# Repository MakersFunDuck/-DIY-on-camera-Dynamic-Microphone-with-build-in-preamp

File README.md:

# DIY on-camera Dynamic micrcophone with build-in preamp

This project is a dynamic microphone utilizing a cloned SM57 capsule. The circuit incorporates a THAT 1510 preamp and is powered by phantom power from the XLR input. It is also compatible with dynamic microphones that require phantom power. If you wish to use it this way, simply cut the solder bridges and connect the appropriate ones. Additionally, I’ve left two pins available in case you prefer to power the circuit externally (e.g., with a battery). You can adjust the gain using the onboard knob.

Capsule which I used :
https://s.click.aliexpress.com/e/_omLsn6Z

Microphone Foam
https://s.click.aliexpress.com/e/_oEmwhu5

## License

 See the [LICENSE](LICENSE) file for details.

inspired from : https://github.com/ojg/thatmicpre

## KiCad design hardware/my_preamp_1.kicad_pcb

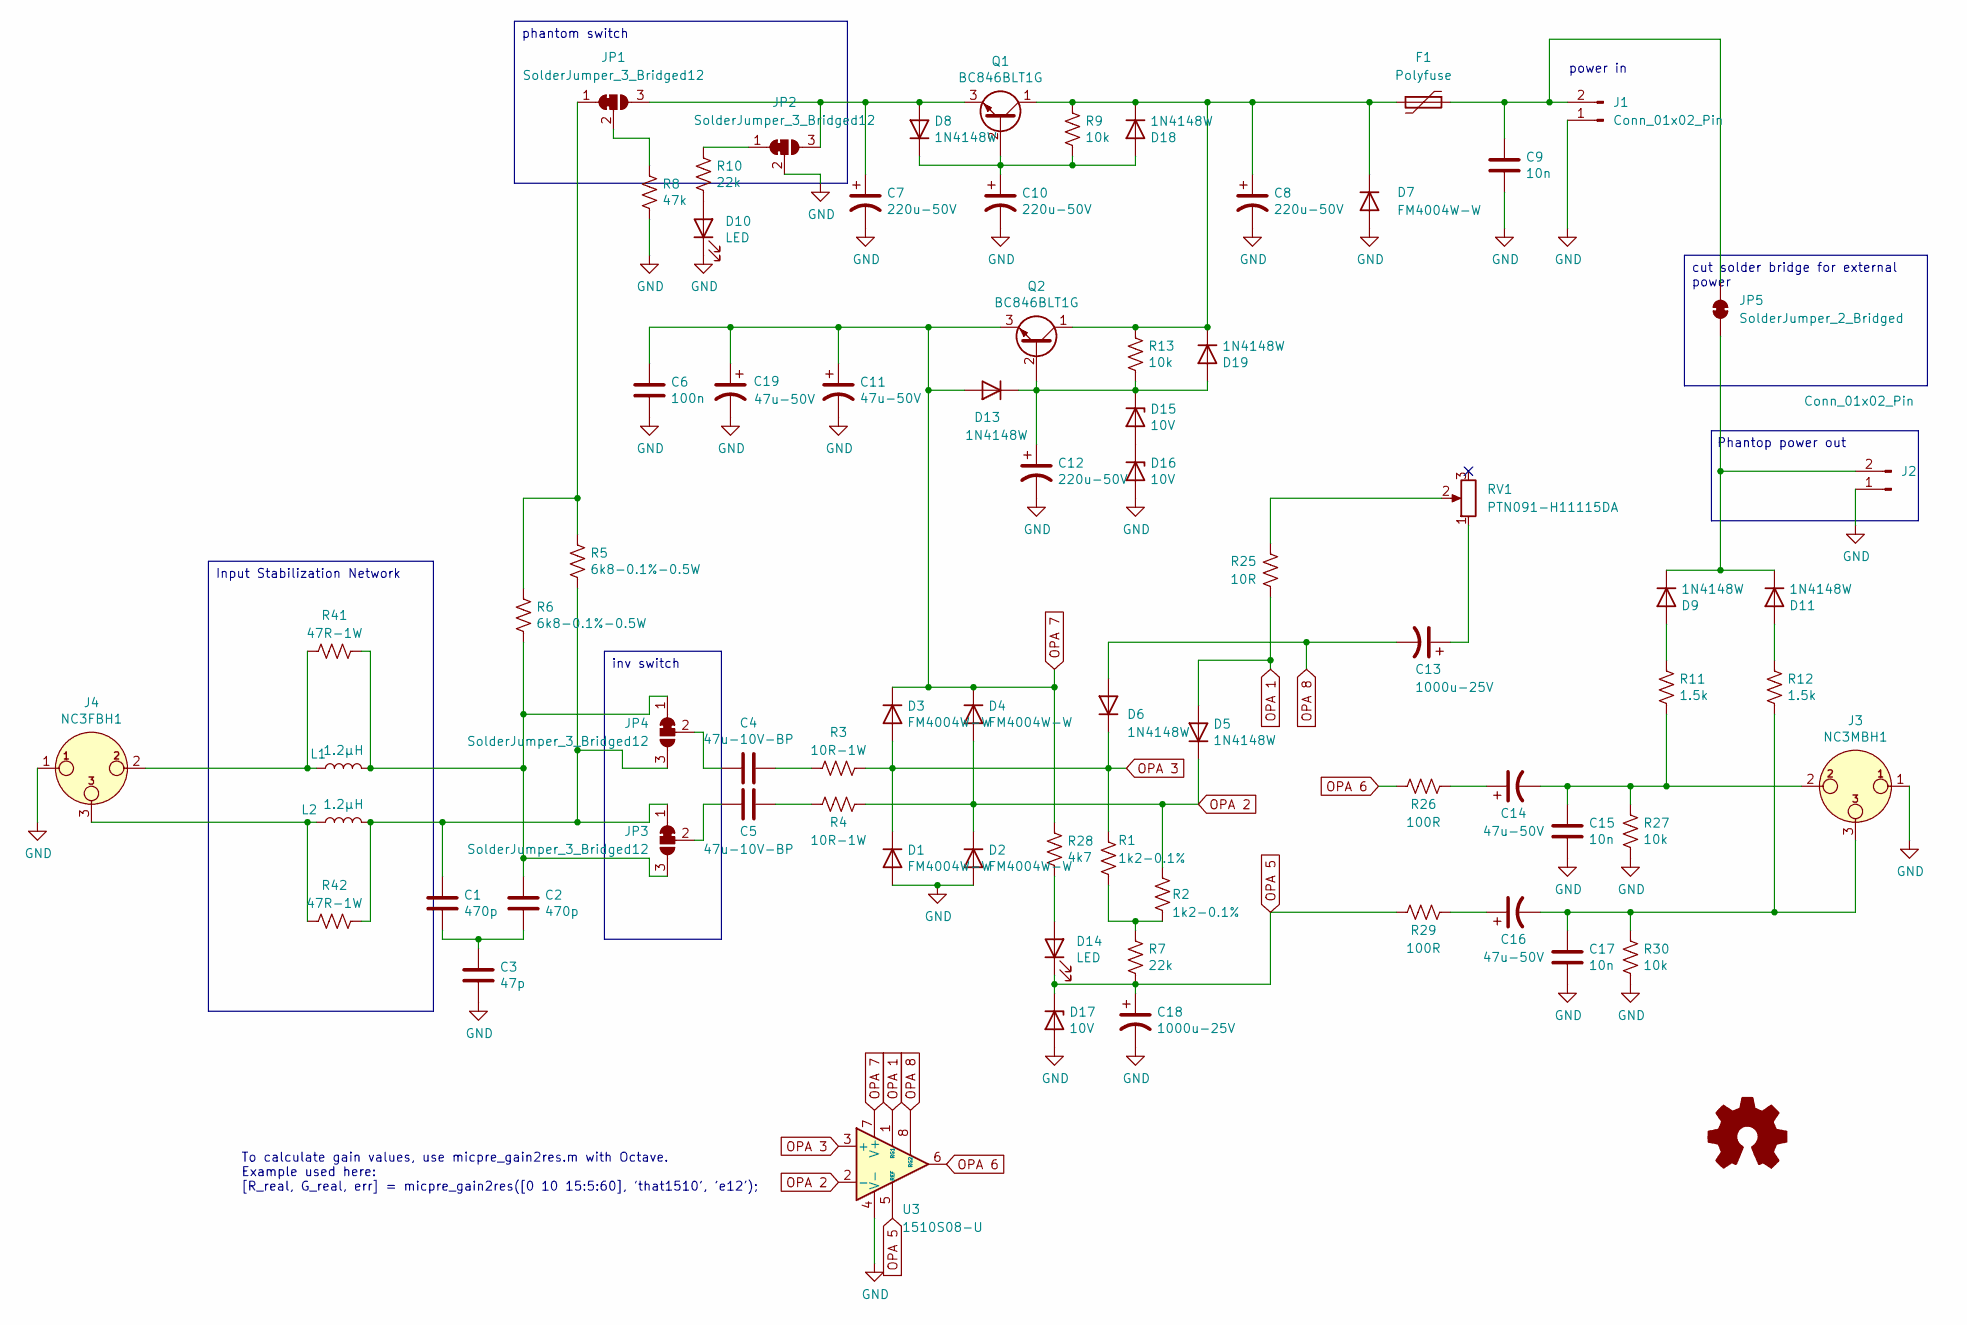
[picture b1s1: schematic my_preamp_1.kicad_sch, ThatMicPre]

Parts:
C1, C2: 470p; C_0805_2012Metric_Pad1.18x1.45mm_HandSolder; Mfr Part Nr ECH-U1H471GX5
C3: 47p; C_0805_2012Metric_Pad1.18x1.45mm_HandSolder; Mfr Part Nr C0805C470J5GAC7210
C4, C5: 47u-10V-BP; CP_Elec_8x5.4; Mfr Part Nr UWP1A470MCL1GB
C6: 100n; C_0805_2012Metric_Pad1.18x1.45mm_HandSolder; Mfr Part Nr KGF21BR71H104KT
C7, C8, C10, C12: 220u-50V; C_Elec_10x10.2; Mfr Part Nr 865080657018
C9, C15, C17: 10n; C_0603_1608Metric_Pad1.08x0.95mm_HandSolder; Mfr Part Nr CC0603MRY5V9BB103
C11, C14, C16, C19: 47u-50V; CP_Elec_8x10.5; Mfr Part Nr ATB476M063
C13, C18: 1000u-25V; C_Elec_10x10.2; Mfr Part Nr EEE-FT1E102UL
D1, D2, D3, D4, D7: FM4004W-W; D_SMA_Handsoldering; Mfr Part Nr FM4004W-W
D5, D6, D8, D9, D11, D13, D18, D19: 1N4148W; D_SOD-123F; Mfr Part Nr 1N4148W
D10, D14: LED; LED_0402_1005Metric_Pad0.77x0.64mm_HandSolder; Mfr Part Nr SML-P12YTT86RR
D15, D16, D17: 10V; D_SOD-323; Mfr Part Nr BZX384-B10-QX
F1: Polyfuse; Fuse_1206_3216Metric_Pad1.42x1.75mm_HandSolder; Mfr Part Nr PTS120660V005
J1, J2: Conn_01x02_Pin; PinHeader_1x02_P2.54mm_Vertical
J3: NC3MBH1; Jack_XLR_Neutrik_NC3MBH-0_Horizontal; Mfr Part Nr NC3MBH
J4: NC3FBH1; Jack_XLR_Neutrik_NC3MAFH-PH_Horizontal; Mfr Part Nr NC3FBH1
JP1, JP2, JP3, JP4: SolderJumper_3_Bridged12; SolderJumper-3_P1.3mm_Bridged12_RoundedPad1.0x1.5mm_NumberL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
JP5: SolderJumper_2_Bridged; SolderJumper-2_P1.3mm_Bridged_RoundedPad1.0x1.5mm
L1, L2: 1.2μH; L_0402_1005Metric_Pad0.77x0.64mm_HandSolder; Mfr Part Nr MLF1005G1R2JTD25
Q1, Q2: BC846BLT1G; SOT-23-3; Mfr Part Nr BC846BLT1G
R1, R2: 1k2-0.1%; R_0402_1005Metric_Pad0.72x0.64mm_HandSolder; Mfr Part Nr RT0402BRD071K21L
R3, R4: 10R-1W; R_0402_1005Metric_Pad0.72x0.64mm_HandSolder; Mfr Part Nr RT0402BRD0710RL
R5, R6: 6k8-0.1%-0.5W; R_0402_1005Metric_Pad0.72x0.64mm_HandSolder; Mfr Part Nr RT0402BRD076K81L
R7, R10: 22k; R_0402_1005Metric_Pad0.72x0.64mm_HandSolder; Mfr Part Nr RE0402DRE0722KL
R8: 47k; R_0402_1005Metric_Pad0.72x0.64mm_HandSolder; Mfr Part Nr RT0402FRE0747KL
R9, R13: 10k; R_0402_1005Metric_Pad0.72x0.64mm_HandSolder; Mfr Part Nr RP0402BRD0747KL
R11, R12: 1.5k; R_0402_1005Metric_Pad0.72x0.64mm_HandSolder; Mfr Part Nr ERA-2APB152X
R25: 10R; R_0402_1005Metric_Pad0.72x0.64mm_HandSolder; Mfr Part Nr RT0402BRD0710RL
R26, R29: 100R; R_0402_1005Metric_Pad0.72x0.64mm_HandSolder; Mfr Part Nr RP0402BRD07100RL
R27, R30: 10k; R_0402_1005Metric_Pad0.72x0.64mm_HandSolder; Mfr Part Nr MCS0402MD1002BE100
R28: 4k7; R_0402_1005Metric_Pad0.72x0.64mm_HandSolder; Mfr Part Nr RP0402BRD074K7L
R41, R42: 47R-1W; R_0402_1005Metric_Pad0.72x0.64mm_HandSolder; Mfr Part Nr RT0402BRD0747R5L
RV1: PTN091-H11115DA; Potentiometer_Vishay_T73XW_Horizontal; Mfr Part Nr PTN091-H11115DA
U3: 1510S08-U; SOIC-8W_5.3x5.3mm_P1.27mm; Mfr Part Nr 1510S08-U

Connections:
GND: C3.2, C6.2, C7.2, C8.2, C9.2, C10.2, C11.2, C12.2, C15.2, C17.2, C18.2, C19.2, D1.2 (A), D2.2 (A), D7.2 (A), D10.1 (K), D16.2 (A), D17.2 (A), J1.1, J2.1, J3.1, J4.1, JP2.2 (C), R8.2, R27.2, R30.2, U3.4 (V-)
unnamed: C1.2, C2.2, C3.1
unnamed: C4.2, R3.2
unnamed: C5.2, R4.2
unnamed: C13.1, RV1.1
unnamed: C14.1, R26.1
unnamed: C14.2, C15.1, J3.2, R11.2, R27.1
unnamed: C16.1, R29.1
unnamed: C16.2, C17.1, J3.3, R12.2, R30.1
unnamed: C7.1, D8.2 (A), JP1.3 (B), JP2.3 (B), Q1.3 (E)
unnamed: D9.2 (A), R11.1
unnamed: D10.2 (A), R10.2
unnamed: D11.2 (A), R12.1
unnamed: D9.1 (K), D11.1 (K), J2.2, JP5.1 (A)
unnamed: C12.1, D13.1 (K), D15.1 (K), D19.2 (A), Q2.2 (B), R13.2
unnamed: D14.2 (A), R28.2
unnamed: D15.2 (A), D16.1 (K)
unnamed: C10.1, D8.1 (K), D18.2 (A), Q1.2 (B), R9.2
unnamed: C8.1, D7.1 (K), D18.1 (K), D19.1 (K), F1.2, Q1.1 (C), Q2.1 (C), R9.1, R13.1
unnamed: C9.1, F1.1, J1.2, JP5.2 (B)
unnamed: J4.2, L1.1, R41.2
unnamed: J4.3, L2.1, R42.2
unnamed: JP1.1 (A), R5.1, R6.1
unnamed: JP1.2 (C), R8.1
unnamed: JP2.1 (A), R10.1
unnamed: C1.1, JP3.1 (A), JP4.3 (B), L2.2, R5.2, R42.1
unnamed: C2.1, JP3.3 (B), JP4.1 (A), L1.2, R6.2, R41.1
unnamed: C5.1, JP3.2 (C)
unnamed: C4.1, JP4.2 (C)
unnamed: R1.2, R2.2, R7.1
unnamed: R25.2, RV1.2
OPA 1: D5.2 (A), R25.1, U3.1 (RG1)
OPA 2: D2.1 (K), D4.2 (A), D5.1 (K), R2.1, R4.1, U3.2 (-)
OPA 3: D1.1 (K), D3.2 (A), D6.1 (K), R1.1, R3.1, U3.3 (+)
OPA 5: C18.1, D14.1 (K), D17.1 (K), R7.2, R29.2, U3.5 (REF)
OPA 6: R26.2, U3.6
OPA 7: C6.1, C11.1, C19.1, D3.1 (K), D4.1 (K), D13.2 (A), Q2.3 (E), R28.1, U3.7 (V+)
OPA 8: C13.2, D6.2 (A), U3.8 (RG2)

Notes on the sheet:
Phantop power out
To calculate gain values, use micpre_gain2res.m with Octave. Example used here: [R_real, G_real, err] = micpre_gain2res([0 10 15:5:60], 'that1510', 'e12');
power in
cut solder bridge for external power
inv switch
Input Stabilization Network
phantom switch

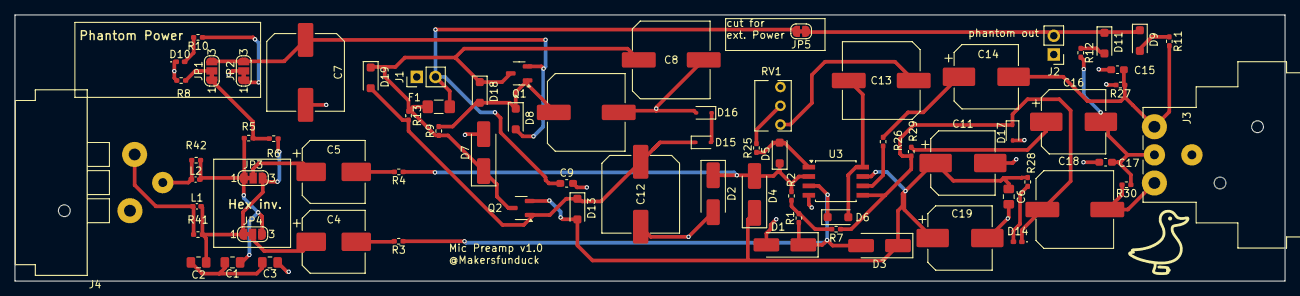
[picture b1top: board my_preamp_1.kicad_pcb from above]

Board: 2 copper layers, 172.0 x 36.1 mm, 74 parts (0 on the bottom side), 38 nets.

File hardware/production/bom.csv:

Designator,Footprint,Quantity,Value,LCSC Part #
"C1, C2",0805,2,470p,
"C10, C12, C7, C8",C_Elec_10x10.2,4,220u-50V,
"C11, C14, C16, C19",CP_Elec_8x10.5,4,47u-50V,
"C13, C18",C_Elec_10x10.2,2,1000u-25V,
"C15, C17, C9",0603,3,10n,
C3,0805,1,47p,
"C4, C5",CP_Elec_8x5.4,2,47u-10V-BP,
C6,0805,1,100n,
"D1, D2, D3, D4, D7",D_SMA_Handsoldering,5,FM4004W-W,
"D10, D14",0402,2,LED,
"D11, D13, D18, D19, D5, D6, D8, D9",D_SOD-123F,8,1N4148W,
"D15, D16",D_SOD-323,2,10V,
D17,D_SOD-323,1,18V,
F1,1206,1,Polyfuse,
"J1, J2",PinHeader_1x02_P2.54mm_Vertical,2,Conn_01x02_Pin,
J3,Jack_XLR_Neutrik_NC3MBH-0_Horizontal,1,NC3MBH1,
J4,Jack_XLR_Neutrik_NC3MBH-1_Horizontal,1,NC3FBH1,
"JP1, JP2, JP3, JP4",SolderJumper-3_P1.3mm_Bridged12_RoundedPad1.0x1.5mm_NumberLabels,4,SolderJumper_3_Bridged12,
"L1, L2",0402,2,1.2μH,
"Q1, Q2",SOT-23-3,2,BC846BLT1G,
"R1, R2",0402,2,1k2-0.1%,
"R10, R7",0402,2,22k,
"R11, R12",0402,2,1.5k,
"R13, R27, R30, R9",0402,4,10k,
R25,0402,1,10R,
"R26, R29",0402,2,100R,
R28,0402,1,4k7,
"R3, R4",0402,2,10R-1W,
"R41, R42",0402,2,47R-1W,
"R5, R6",0402,2,6k8-0.1%-0.5W,
R8,0402,1,47k,
RV1,Potentiometer_Vishay_T73XW_Horizontal,1,PTN091-H11115DA,
U3,SOIC-8W_5.3x5.3mm_P1.27mm,1,1510S08-U,

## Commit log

2025-03-27 first cimmit
    first cimmit
